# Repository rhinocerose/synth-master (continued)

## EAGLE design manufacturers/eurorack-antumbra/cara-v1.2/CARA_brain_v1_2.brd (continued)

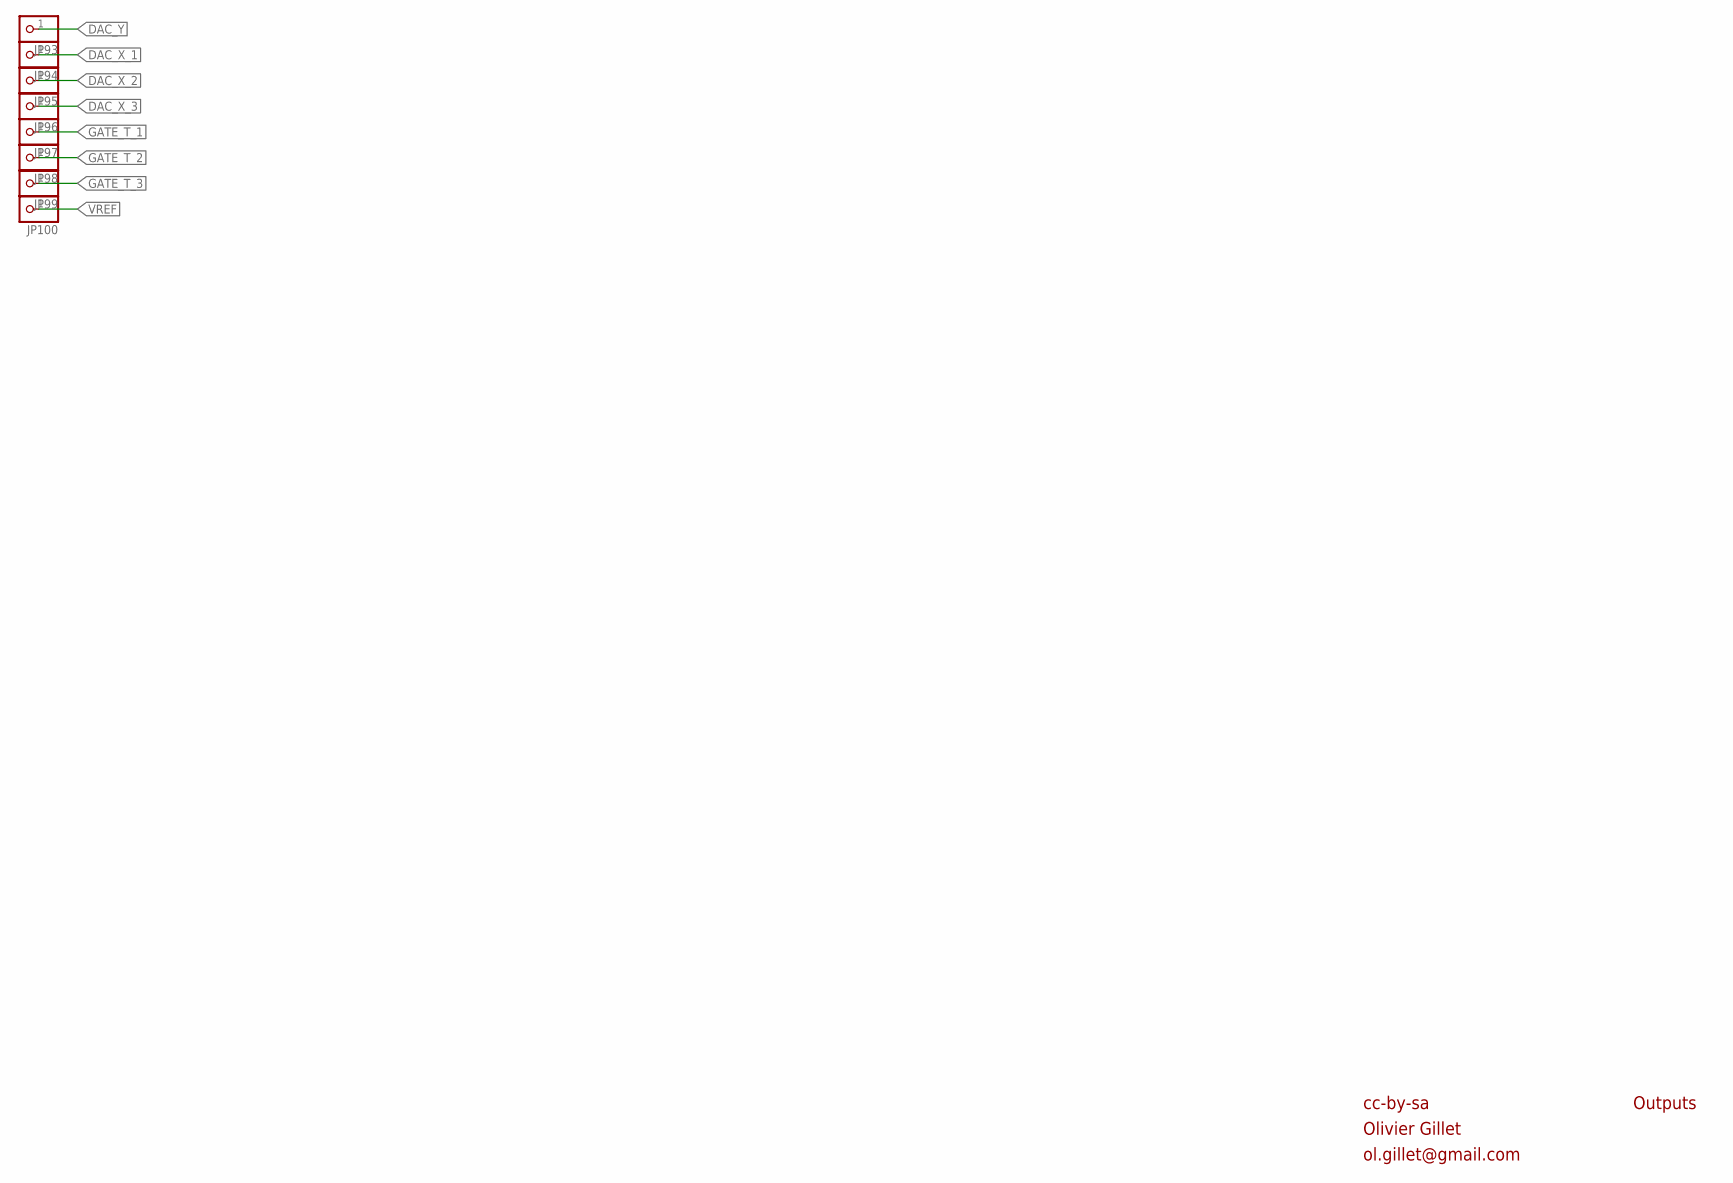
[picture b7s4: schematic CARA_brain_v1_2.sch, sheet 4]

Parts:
JP93, JP94, JP95, JP96, JP97, JP98, JP99, JP100: PINHD-1X1; 1X01

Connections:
DAC_X_1: JP94.1; also elsewhere on the board
DAC_X_2: JP95.1; also elsewhere on the board
DAC_X_3: JP96.1; also elsewhere on the board
DAC_Y: JP93.1; also elsewhere on the board
GATE_T_1: JP97.1; also elsewhere on the board
GATE_T_2: JP98.1; also elsewhere on the board
GATE_T_3: JP99.1; also elsewhere on the board
VREF: JP100.1; also elsewhere on the board

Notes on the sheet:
cc-by-sa
Olivier Gillet
ol.gillet@gmail.com
Outputs

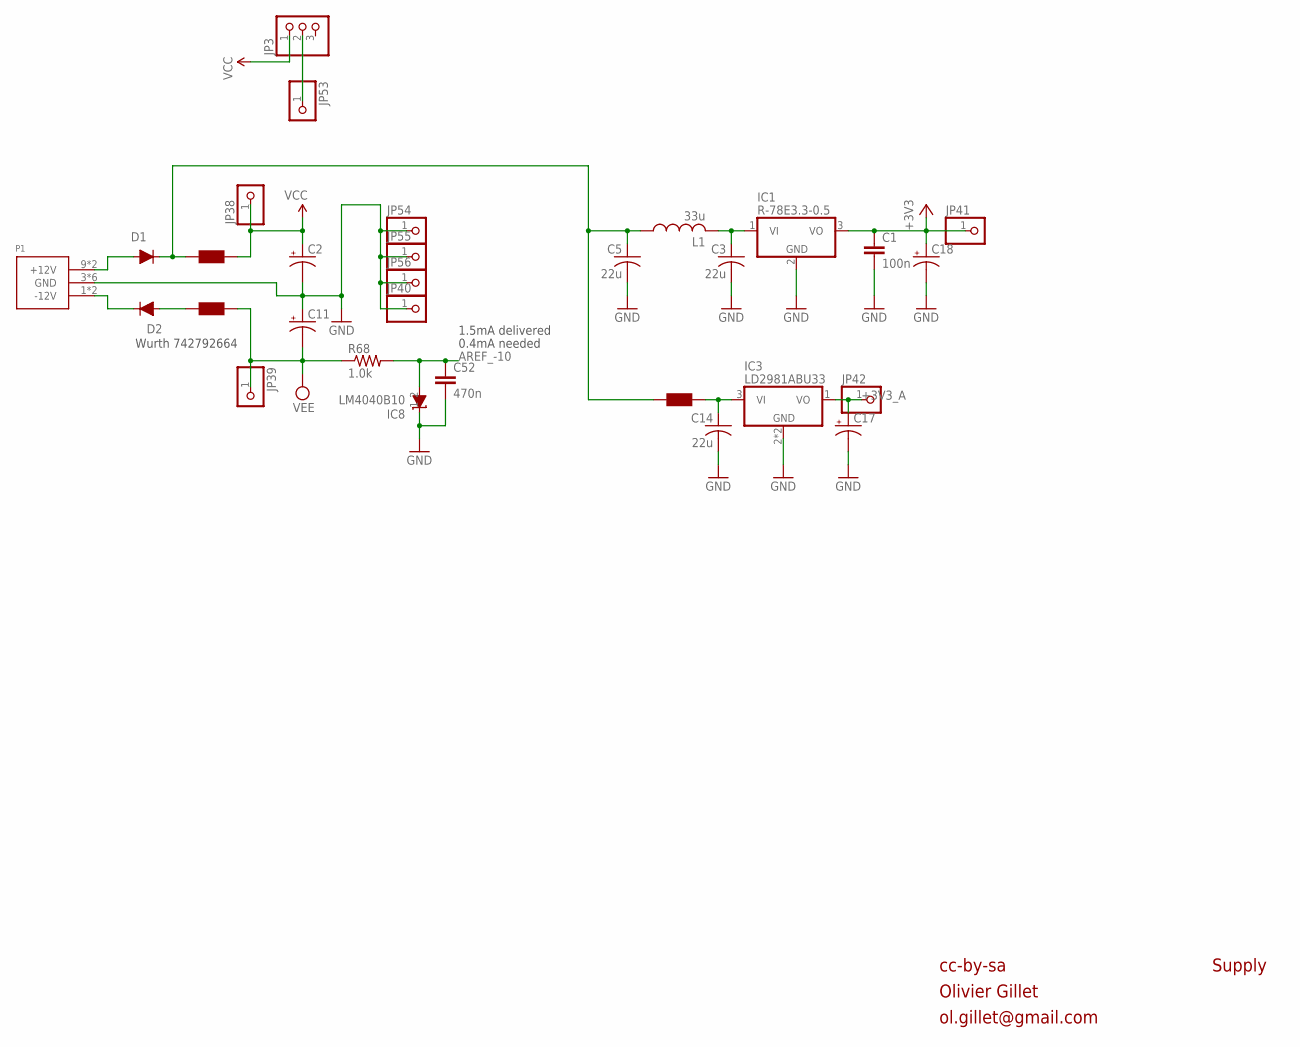
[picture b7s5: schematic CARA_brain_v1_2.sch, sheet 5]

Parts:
C1: 100n; RESISTOR_0603
C2, C11, C17, C18: CAP_POLC; PANASONIC_C
C3, C5, C14: 22u; C1206
C52: 470n; RESISTOR_0603
D1, D2: 1N5819HW; SOD123
F1, F2, F3: FERRITE-BEAD; RESISTOR_0603
IC1: R-78E3.3-0.5; WE78
IC3: LD2981ABU33; SOT89
IC8: LM4040B10; SOT23
JP3: PINHD-1X3; 1X03
JP38, JP39, JP40, JP41, JP42, JP53, JP54, JP55, JP56: PINHD-1X1; 1X01
L1: 33u; L2012C
P1: POWER_SIMPLE10; POWER_10
R68: 1.0k; RESISTOR_0603

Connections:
+3V3: C1.1, C18.+, IC1.3 (VO), JP41.1; also elsewhere on the board
+3V3_A: C17.+, IC3.1 (VO), JP42.1; also elsewhere on the board
AREF_-10: C52.1, IC8.2 (A), R68.2; also elsewhere on the board
GND: C1.2, C2.-, C3.2, C5.2, C11.+, C14.2, C17.-, C18.-, C52.2, IC1.2 (GND), IC3.2 (GND), IC3.2@1 (GND), IC8.1 (C), JP40.1, JP54.1, JP55.1, JP56.1, P1.3 (GND), P1.4 (GND), P1.5 (GND), P1.6 (GND), P1.7 (GND), P1.8 (GND); also elsewhere on the board
unnamed: D1.+, P1.9 (+12V), P1.10 (+12V)
unnamed: D2.-, P1.1 (-12V), P1.2 (-12V)
unnamed: JP3.2, JP53.1
unnamed: C14.1, F3.1, IC3.3 (VI)
unnamed: C5.1, D1.-, F1.2, F3.2, L1.1
unnamed: D2.+, F2.2
unnamed: C3.1, IC1.1 (VI), L1.2
VCC: C2.+, F1.1, JP3.1, JP38.1
VEE: C11.-, F2.1, JP39.1, R68.1

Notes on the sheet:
0.4mA needed
cc-by-sa
Olivier Gillet
ol.gillet@gmail.com
Supply
Wurth 742792664
1.5mA delivered

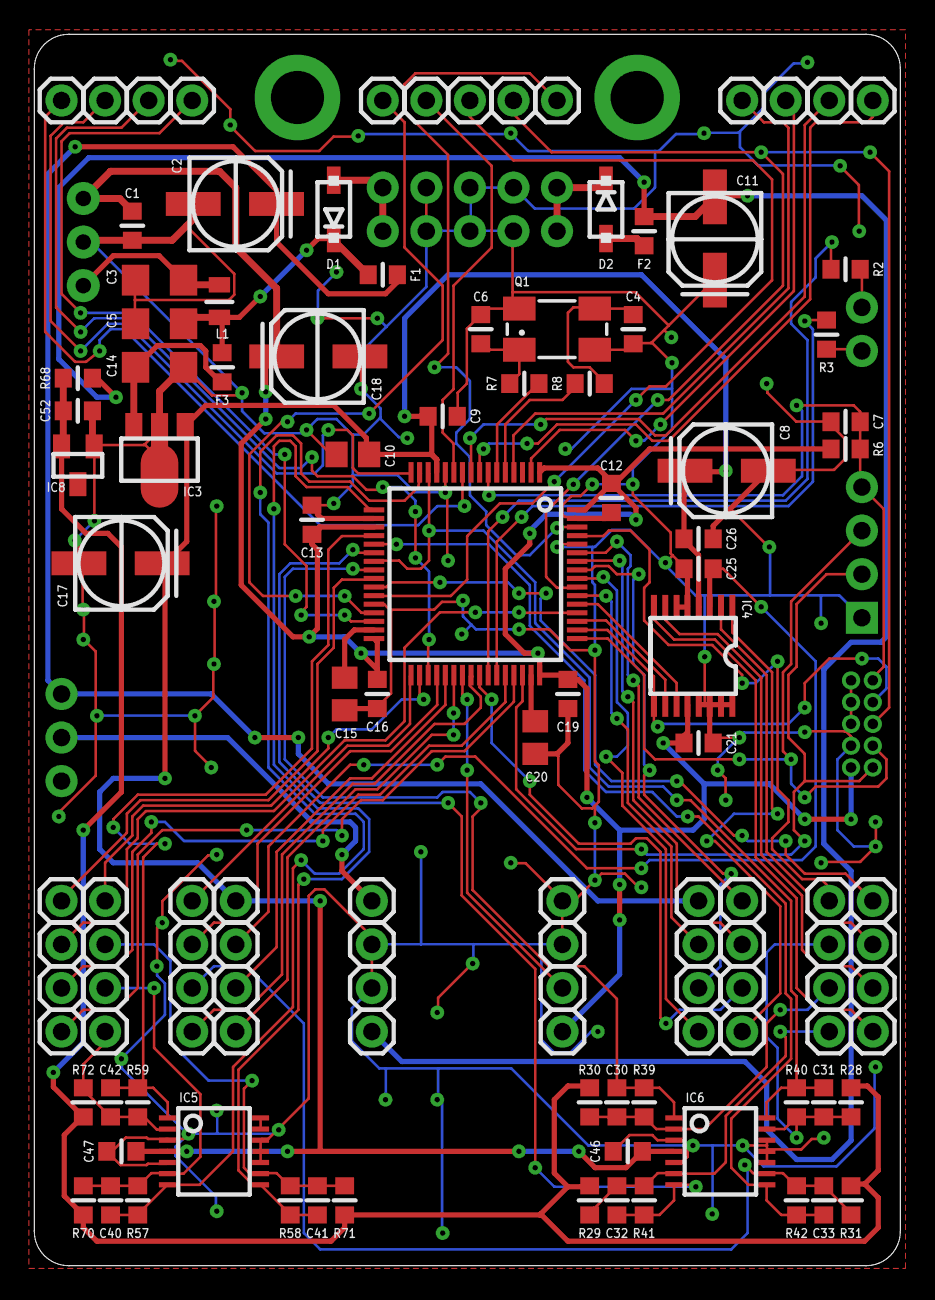
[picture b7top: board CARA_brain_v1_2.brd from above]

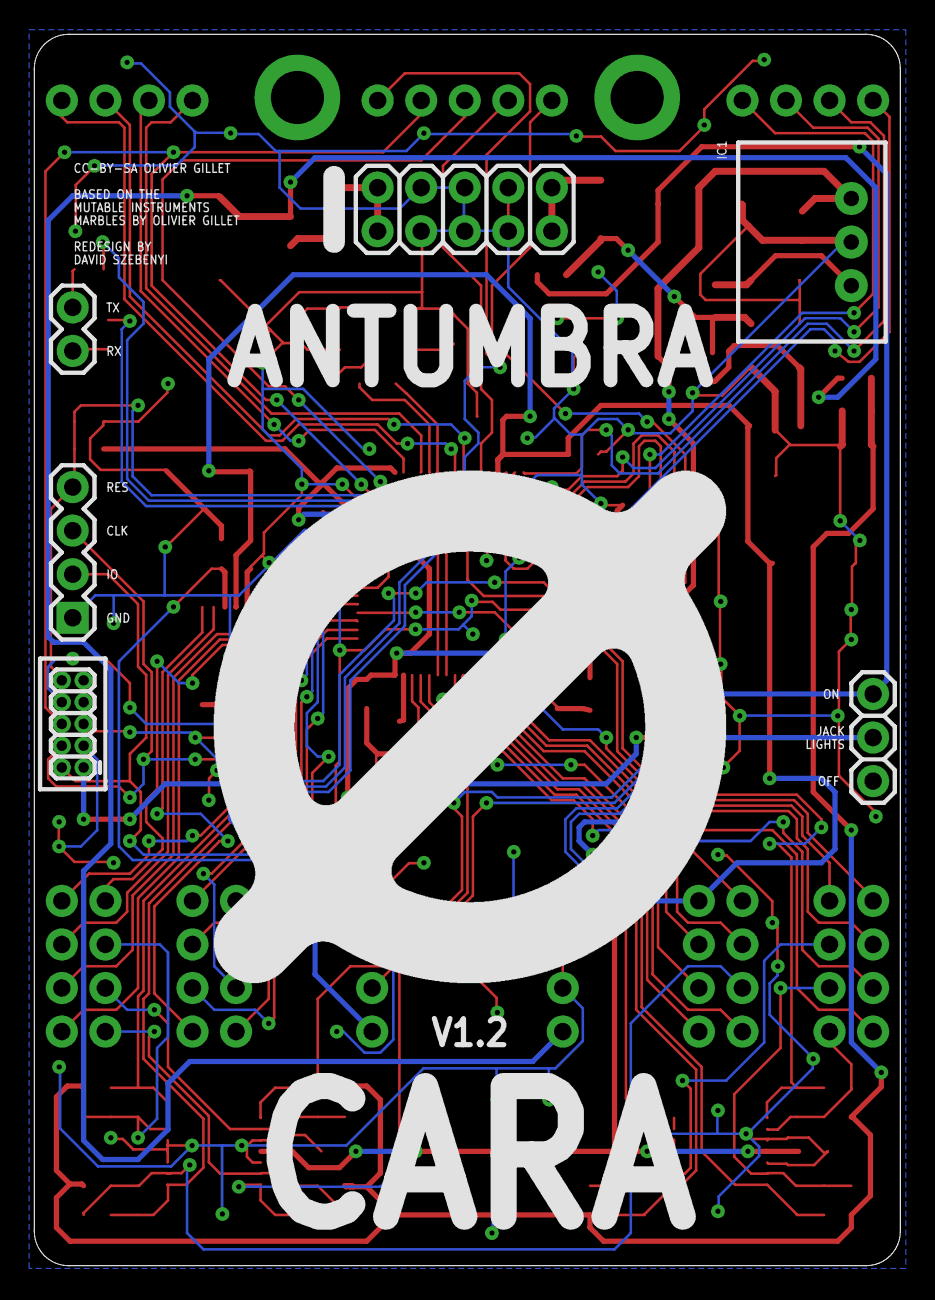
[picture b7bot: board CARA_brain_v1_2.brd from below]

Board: 2 copper layers, 50.5 x 71.8 mm, 128 parts (7 on the bottom side), 81 nets.

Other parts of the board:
U$1: LOGO_30

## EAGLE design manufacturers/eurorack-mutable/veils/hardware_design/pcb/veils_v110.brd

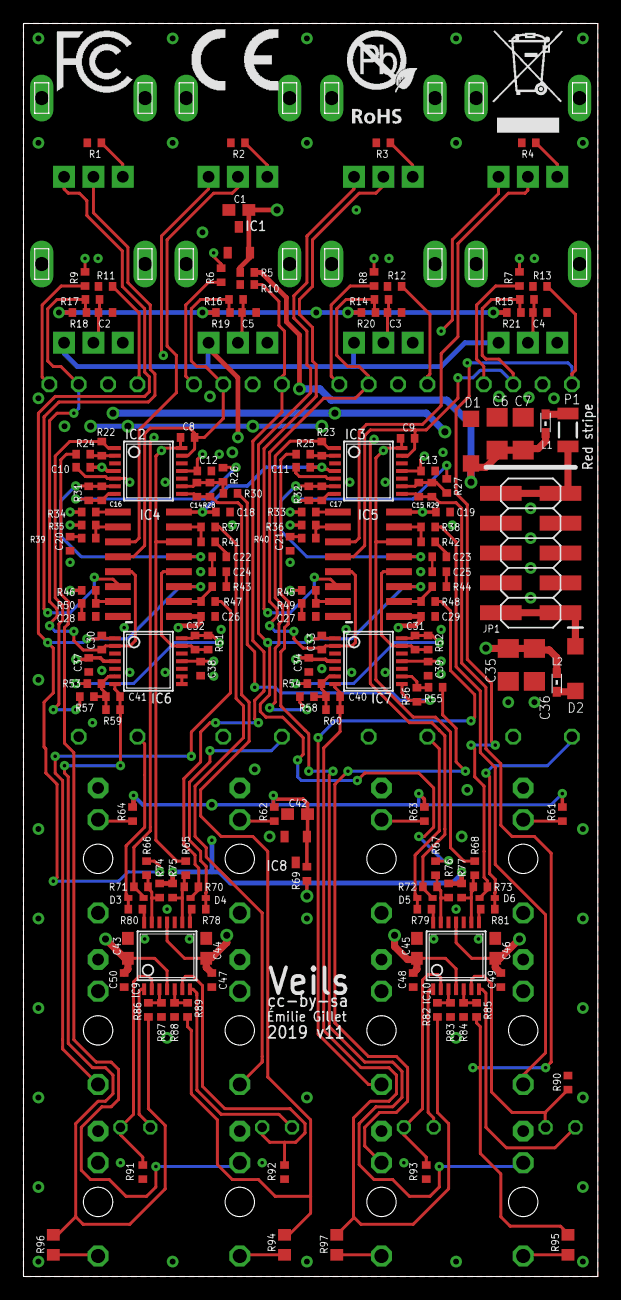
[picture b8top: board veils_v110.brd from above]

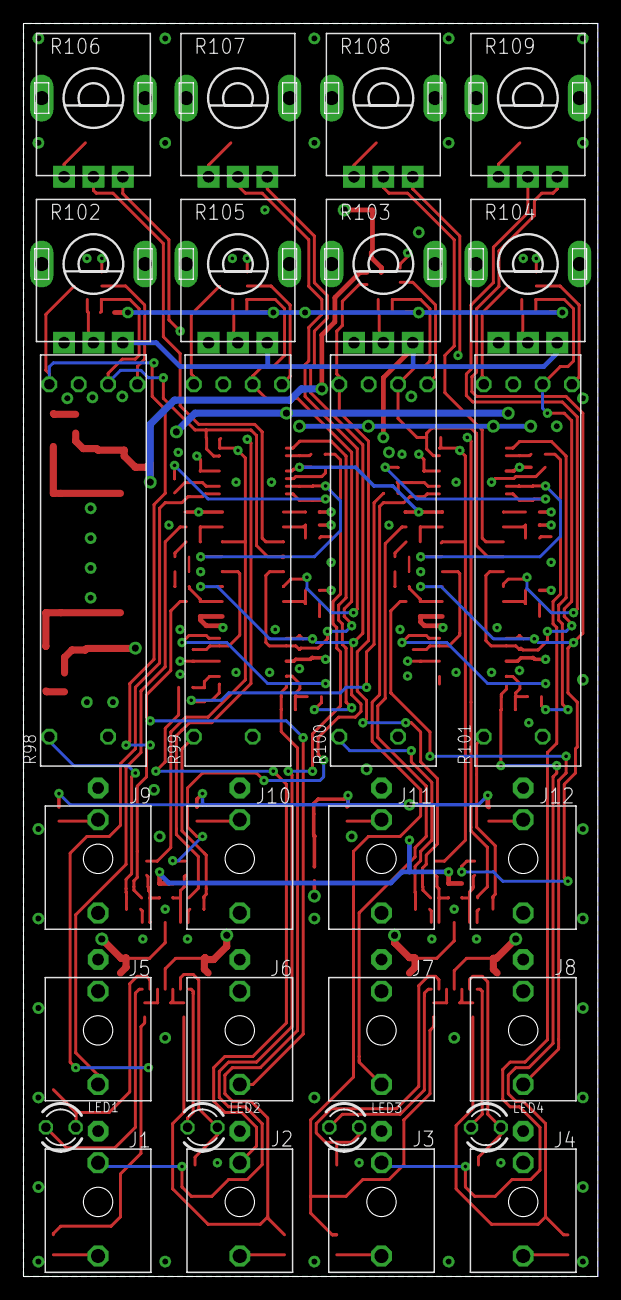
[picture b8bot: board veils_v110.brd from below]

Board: 4 copper layers, 48.9 x 106.7 mm, 199 parts (28 on the bottom side), 121 nets.

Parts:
C1, C42, C43, C44, C45, C46: 2.2u; C0603
C2, C3, C4, C5, C10, C11, C12, C13, C18, C19, C26, C29, C34, C37, C38, C39, C47, C48, C49, C50: 100n; C0402
C6, C7, C35, C36: 22u; C1206
C8, C9, C14, C15, C16, C17, C30, C31, C32, C33, C40, C41: 100p; C0402
C20, C21, C22, C23, C24, C25, C27, C28: 560p; C0402
D1, D2: 1N5819HW; SOD123
D3, D4, D5, D6: 1N4148; SOD523
IC1: LM4040B25; DBZ_R-PDSO-G3
IC2, IC3, IC6, IC7: OPA1679; TSSOP14_065
IC4, IC5: V2164SZ; SOIC16N
IC8: LM4040B10; DBZ_R-PDSO-G3
IC9, IC10: LM324PW; TSSOP14_065
J1, J2, J3, J4, J5, J6, J7, J8, J9, J10, J11, J12: PJ301_THONKICONNTME; WQP_PJ_301M_TME
JP1: M05X2SMD; 2X5-SMD
L1, L2: 742792664; 0603
LED1, LED2, LED3, LED4: 3BC-F; LED3MM
P1: PTCSMD; PTC-1206
R1, R2, R3, R4: 2.0k; R0402
R5, R10, R11, R12, R13, R61, R62, R63, R64, R78, R79, R80, R81: 24.9k; R0402
R6, R7, R8, R9: 100k; R0402
R14, R15, R16, R17: 120k; R0402
R18, R19, R20, R21: 20M; R0402
R22, R23, R56: 5.6k; R0402
R24, R25, R26, R27, R28, R29, R30, R53, R54, R55, R57, R58, R59, R60: 5.1k; R0402
R31, R32, R35, R36, R37, R38, R45, R46, R47, R48, R51, R52: 49.9k; R0402
R33, R34: 680k; R0402
R39, R40, R41, R42, R43, R44, R49, R50, R69: 510; R0402
R65, R66, R67, R68, R70, R71, R72, R73, R74, R75, R76, R77, R82, R83, R84, R85, R86, R87, R88, R89: 1.0M; R0402
R90, R91, R92, R93: 1.2k; R0402
R94, R95, R96, R97: 510; R0603
R98, R99, R100, R101: 20kB; BOURNS_SLIDER
R102, R103, R104, R105: 50kB; ALPS_POT_NARROW
R106, R107, R108, R109: 10kB; ALPS_POT_NARROW
U$1: CE_MEDIUM
U$2: FCC_MEDIUM
U$3: ROHS_LOGO
U$4: TRASHCAN_LOGO

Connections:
1_TO_2: IC3.1, R23.1, R58.2
2_TO_3: IC7.8, R30.2, R56.1
3_TO_4: IC2.1, R22.1, R57.2
AREF_+10: C42.1, IC8.1, R61.2, R62.2, R63.2, R64.2, R69.2, R102.P$1, R103.P$1, R104.P$1, R105.P$1
AREF_-2.5: C1.1, IC1.2, R5.2, R18.2, R19.2, R20.2, R21.2, R35.2, R36.2, R45.2, R46.2, R74.1, R75.1, R76.1, R77.1
CV_IN_1: J9.P3, R7.2
FOO: IC5.2, R36.1, R40.2
FOO1: IC5.7, R45.1, R49.2
FOO2: IC4.2, R35.1, R39.2
FOO3: IC4.7, R46.1, R50.2
GND: C1.2, C2.2, C3.2, C4.2, C5.2, C6.1, C7.1, C10.2, C11.2, C12.1, C13.1, C18.2, C19.2, C20.2, C21.2, C22.2, C23.2, C24.2, C25.2, C26.1, C27.2, C28.2, C29.1, C34.2, C35.2, C36.2, C37.2, C38.1, C39.1, C42.2, C43.2, C44.1, C45.2, C46.1, C47.1, C48.2, C49.1, C50.2, D1.C, IC1.1, IC2.3, IC2.5, IC2.10, IC2.12, IC3.3, IC3.5, IC3.10, IC3.12, IC4.8, IC5.8, IC6.3, IC6.5, IC6.10, IC6.12, IC7.3, IC7.5, IC7.10, IC7.12, IC8.2, IC9.10, IC9.12, IC10.10, IC10.12, J1.P1, J2.P1, J3.P1, J4.P1, J5.P1, J5.P2, J6.P1, J6.P2, J7.P1, J7.P2, J8.P1, J8.P2, J9.P1, J10.P1, J11.P1, J12.P1, JP1.3, JP1.4, JP1.5, JP1.6, JP1.7, JP1.8, R1.1, R2.1, R3.1, R4.1, R10.2, R11.2, R12.2, R13.2, R83.1, R84.1, R87.1, R88.1, R90.2, R91.2, R92.2, R93.2, R98.3, R99.3, R100.3, R101.3, R102.P$3, R103.P$3, R104.P$3, R105.P$3
unnamed: IC10.5, R84.2, R85.2
unnamed: IC6.8, IC6.9
unnamed: J6.P3, R48.2
unnamed: IC10.3, R82.2, R83.2
unnamed: IC9.5, R88.2, R89.2
unnamed: J2.P3, R97.1
unnamed: J1.P3, R95.1
unnamed: IC9.3, R86.2, R87.2
unnamed: IC5.3, R106.P$2
unnamed: C15.1, IC3.9, R27.1, R29.2
unnamed: D2.A, JP1.1, JP1.2
unnamed: JP1.9, JP1.10, P1.2
unnamed: L1.2, P1.1
unnamed: C4.1, R15.2, R102.P$2
unnamed: R4.2, R106.P$3
unnamed: D2.C, L2.2
unnamed: C25.1, R44.1
unnamed: IC10.7, LED1.K
unnamed: IC10.6, LED1.A, R90.1
unnamed: C21.1, R40.1
unnamed: J10.P2, R63.1
unnamed: IC3.2, R23.2, R25.1
unnamed: J3.P3, R94.1
unnamed: IC5.10, R44.2, R48.1
unnamed: J1.P2, R25.2
unnamed: IC5.6, R107.P$2
unnamed: C40.1, IC7.6, R54.1, R58.1, R60.2
unnamed: IC5.1, R33.2
unnamed: IC4.3, R108.P$2
unnamed: J9.P2, R61.1
unnamed: R7.1, R98.2
unnamed: R3.2, R107.P$3
unnamed: R8.1, R99.2
unnamed: R2.2, R108.P$3
unnamed: IC10.1, LED2.K
unnamed: IC10.2, LED2.A, R93.1
unnamed: IC7.9, R55.1, R56.2
unnamed: J2.P2, R55.2
unnamed: C31.2, IC7.14, R52.1, R54.2
unnamed: J10.P3, R8.2
unnamed: C27.1, R49.1
unnamed: C33.1, IC5.5, IC7.2, R14.1, R20.1, R99.1
unnamed: IC4.6, R109.P$2
unnamed: J11.P3, R6.2
unnamed: C22.1, R41.1
unnamed: IC4.15, R37.1, R41.2
unnamed: C23.1, R42.1
unnamed: J12.P2, R64.1
unnamed: C14.1, IC2.9, R26.1, R28.2, R30.1
unnamed: IC10.8, R81.1
unnamed: R1.2, R109.P$3
unnamed: J7.P3, R37.2
unnamed: C31.1, IC5.12, IC7.13, R52.2
unnamed: D6.A, R13.1, R73.2, R98.E
unnamed: J12.P3, R9.2
unnamed: C16.1, IC2.6, IC4.13, R31.2
unnamed: IC10.9, R68.2, R73.1, R77.2
unnamed: IC9.7, LED3.K
unnamed: IC9.6, LED3.A, R92.1
unnamed: IC2.2, R22.2, R24.1
unnamed: J3.P2, R24.2
unnamed: C32.1, IC4.12, IC6.13, R51.2
unnamed: C20.1, R39.1
unnamed: R6.1, R100.2
unnamed: C9.1, IC3.13, IC5.4, R15.1, R21.1, R98.1
unnamed: J5.P3, R38.2
unnamed: C8.1, IC2.13, IC4.4, R16.1, R19.1, R100.1
unnamed: D5.A, R12.1, R72.2, R99.E
unnamed: J8.P3, R47.2
unnamed: R9.1, R101.2
unnamed: J4.P3, R96.1
unnamed: C24.1, R43.1
unnamed: IC4.10, R43.2, R47.1
unnamed: IC10.14, R79.1
unnamed: IC5.15, R38.1, R42.2
unnamed: C41.1, IC6.6, R53.1, R57.1, R59.2
unnamed: C9.2, IC3.14, IC5.14, R68.1, R106.P$1
unnamed: IC10.13, R67.2, R72.1, R76.2
unnamed: IC9.8, R78.1
unnamed: C33.2, IC5.11, IC7.1, R67.1, R107.P$1
unnamed: IC4.1, R34.2
unnamed: D4.A, R10.1, R70.2, R100.E
unnamed: IC9.9, R65.2, R70.1, R75.2
unnamed: IC9.1, LED4.K
unnamed: IC9.2, LED4.A, R91.1
unnamed: IC9.14, R80.1
unnamed: C8.2, IC2.14, IC4.14, R65.1, R108.P$1
unnamed: C32.2, IC6.14, R51.1, R53.2
unnamed: J11.P2, R62.1
unnamed: C28.1, R50.1
unnamed: C30.1, IC4.5, IC6.2, R17.1, R18.1, R101.1
unnamed: D3.A, R11.1, R71.2, R101.E
unnamed: IC9.13, R66.2, R71.1, R74.2
unnamed: C30.2, IC4.11, IC6.1, R66.1, R109.P$1
unnamed: C17.1, IC3.6, IC5.13, R32.2
unnamed: C17.2, IC3.7, R27.2, R32.1
unnamed: C3.1, R14.2, R105.P$2
unnamed: C5.1, R16.2, R103.P$2
unnamed: C16.2, IC2.7, R26.2, R31.1
unnamed: C2.1, R17.2, R104.P$2
OUT1: C15.2, IC3.8, R29.1, R85.1, R95.2
OUT2: C40.2, IC7.7, R60.1, R82.1, R97.2
OUT3: C14.2, IC2.8, R28.1, R89.1, R94.2
OUT4: C41.2, IC6.7, R59.1, R86.1, R96.2
PROT1: D6.C, R81.2, R98.B
PROT2: D5.C, R79.2, R99.B
PROT3: D4.C, R78.2, R100.B
PROT4: D3.C, R80.2, R101.B
VCC: C10.1, C11.1, C18.1, C19.1, C34.1, C35.1, C36.1, C37.1, C43.1, C45.1, C48.1, C50.1, IC2.4, IC3.4, IC4.16, IC5.16, IC6.4, IC7.4, IC9.4, IC10.4, L2.1, R33.1, R34.1, R69.1
VEE: C6.2, C7.2, C12.2, C13.2, C26.2, C29.2, C38.2, C39.2, C44.2, C46.2, C47.2, C49.2, D1.A, IC2.11, IC3.11, IC4.9, IC5.9, IC6.11, IC7.11, IC9.11, IC10.11, L1.1, R5.1

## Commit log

2022-02-01 Started adding manufacturer repos
2022-02-01 removed individual jakplugg repos
2022-02-01 Added all 4ms repos
2022-02-03 Added minisystem, removed westlicht submodules
2022-02-03 Removed libs
2022-04-25 Removed some git files
2022-04-25 Cleaned git files
2023-01-18 Pushing
